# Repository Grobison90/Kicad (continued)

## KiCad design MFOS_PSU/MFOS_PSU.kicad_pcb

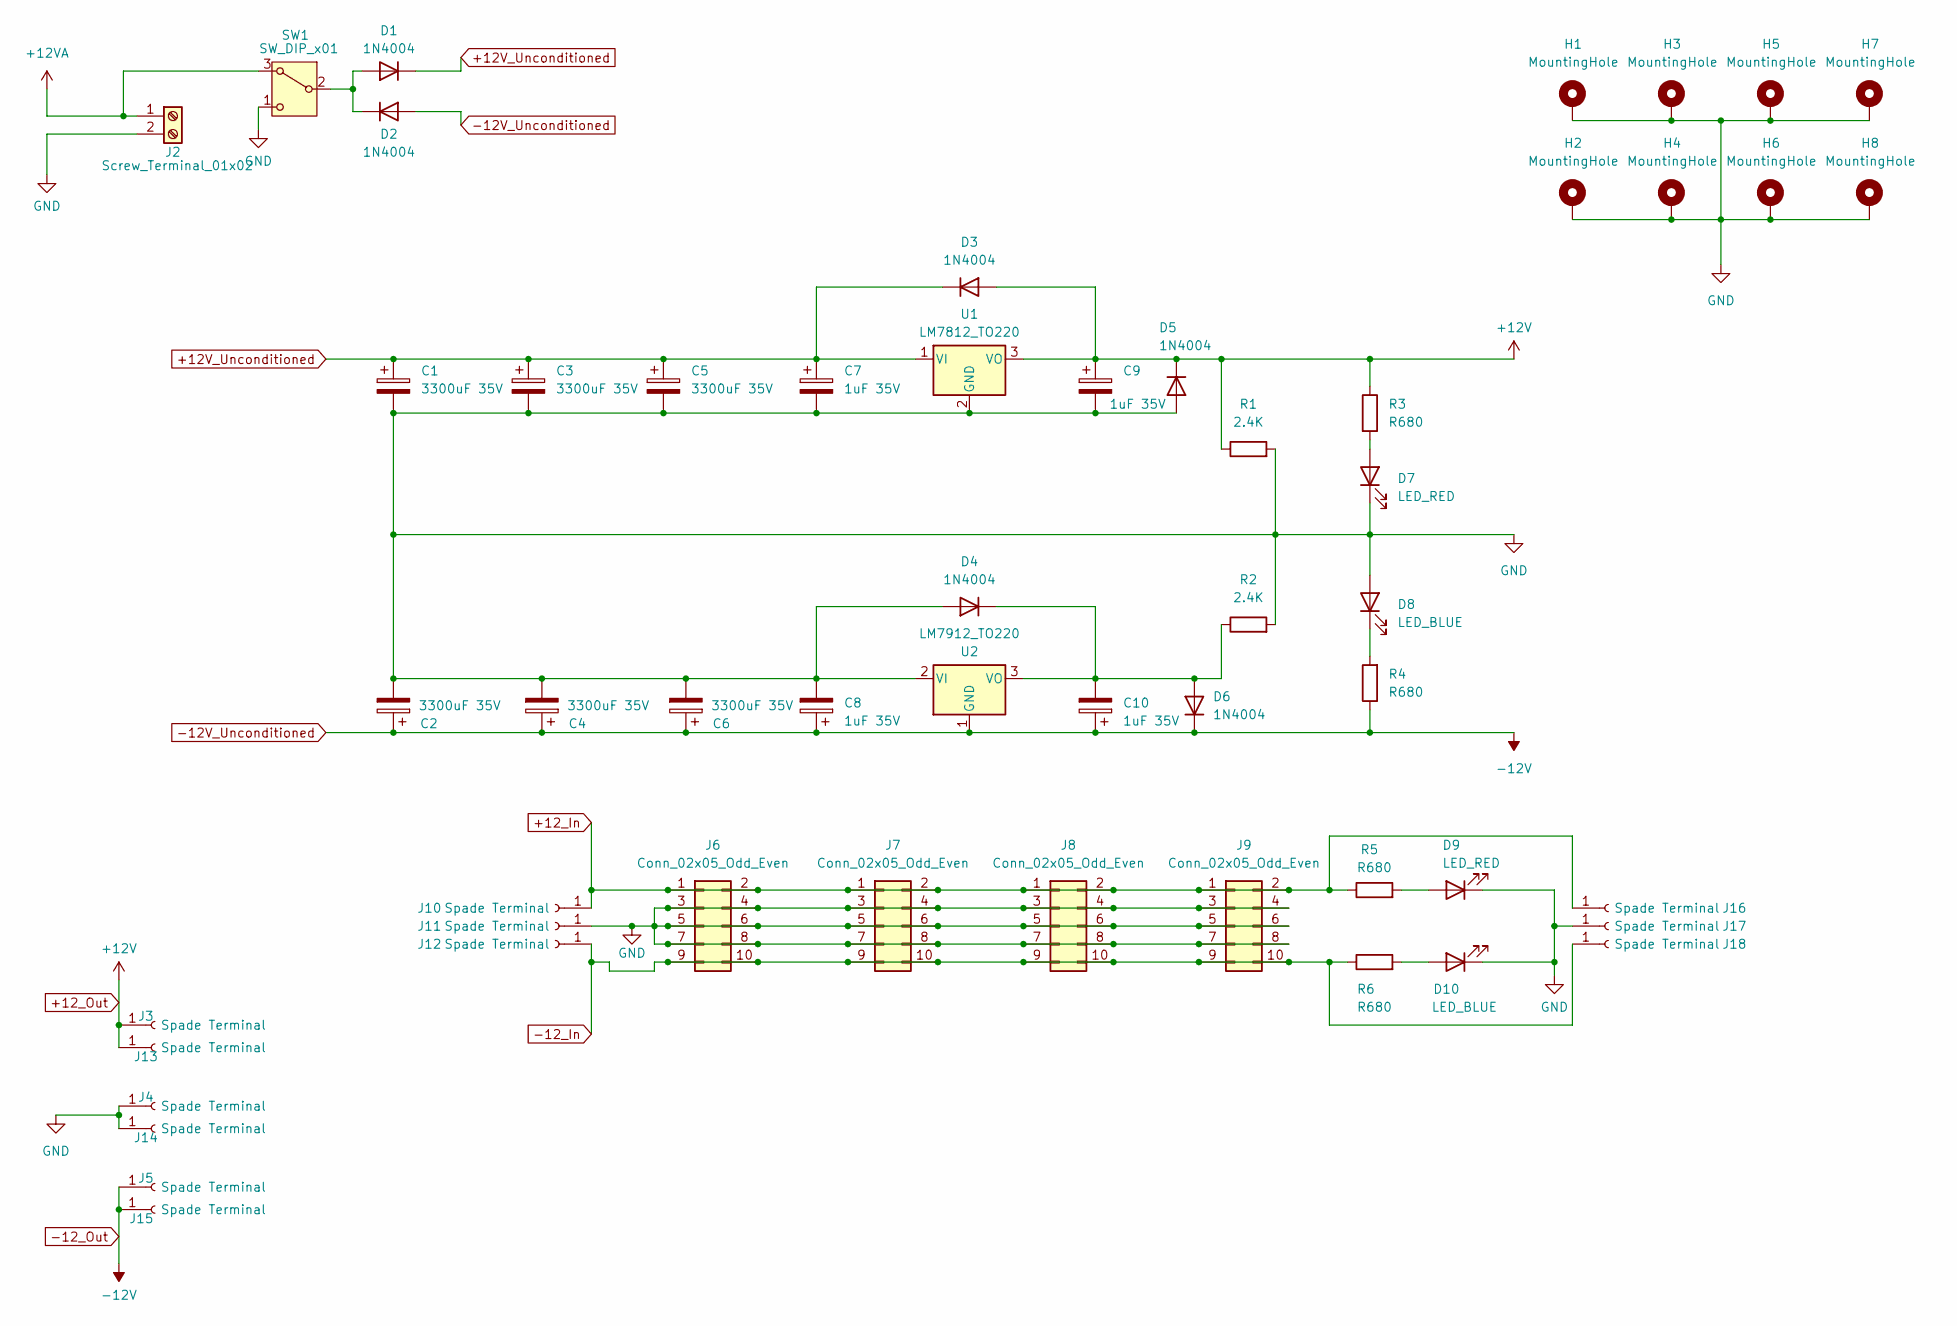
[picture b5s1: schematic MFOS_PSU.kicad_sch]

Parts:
C1, C2, C3, C4, C5, C6: 3300uF 35V; CP_Radial_D18.0mm_P7.50mm
C7, C8, C9, C10: 1uF 35V; CP_Radial_Tantal_D5.0mm_P2.50mm
D1, D2: 1N4004; D_DO-41_SOD81_P10.16mm_Horizontal
D3, D4: 1N4004; D_DO-41_SOD81_P5.08mm_Vertical_KathodeUp
D5, D6: 1N4004; D_DO-41_SOD81_P3.81mm_Vertical_KathodeUp
D7, D9: LED_RED; LED_D5.0mm
D8, D10: LED_BLUE; LED_D5.0mm
H1, H2, H3, H4, H5, H6, H7, H8: MountingHole; MountingHole_2.2mm_M2_Pad
J2: Screw_Terminal_01x02; BarrelJack_CUI_PJ-063AH_Horizontal
J3, J4, J5, J10, J11, J12, J13, J14, J15, J16, J17, J18: Spade Terminal; Spade Connector_Horizontal
J6, J7, J8, J9: Conn_02x05_Odd_Even; Eurorack Power (IDC p=2.54)_Text
R1, R2: 2.4K; R_Axial_DIN0207_L6.3mm_D2.5mm_P2.54mm_Vertical
R3, R4, R5, R6: R680; R_Axial_DIN0207_L6.3mm_D2.5mm_P2.54mm_Vertical
SW1: SW_DIP_x01; Slide Switch A-3698
U1: LM7812_TO220; TO-220-3_Vertical
U2: LM7912_TO220; TO-220-3_Vertical

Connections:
+12VA: J2.1, SW1.3 (A)
+12V_Unconditioned: C1.1, C3.1, C5.1, C7.1, D1.1 (K), D3.1 (K), U1.1 (VI)
+12_In: J6.1, J6.2, J7.1, J7.2, J8.1, J8.2, J9.1, J9.2, J10.1, J16.1, R5.1
+12_Out: C9.1, D3.2 (A), D5.1 (K), J3.1, J13.1, R1.1, R3.1, U1.3 (VO)
-12V_Unconditioned: C2.1, C4.1, C6.1, C8.1, C10.1, D2.2 (A), D6.1 (K), J5.1, J15.1, R4.1, U2.1 (GND)
-12_In: J6.9, J6.10, J7.9, J7.10, J8.9, J8.10, J9.9, J9.10, J12.1, J18.1, R6.1
GND: C1.2, C2.2, C3.2, C4.2, C5.2, C6.2, C7.2, C8.2, C9.2, D4.2 (A), D5.2 (A), D7.1 (K), D8.2 (A), D9.1 (K), D10.1 (K), H1.1, H2.1, H3.1, H4.1, H5.1, H6.1, H7.1, H8.1, J2.2, J4.1, J6.3, J6.4, J6.5, J6.6, J6.7, J6.8, J7.3, J7.4, J7.5, J7.6, J7.7, J7.8, J8.3, J8.4, J8.5, J8.6, J8.7, J8.8, J9.3, J9.4, J9.5, J9.6, J9.7, J9.8, J11.1, J14.1, J17.1, R1.2, R2.2, SW1.1 (C), U1.2 (GND), U2.2 (VI)
unnamed: D1.2 (A), D2.1 (K), SW1.2 (B)
unnamed: C10.2, D4.1 (K), D6.2 (A), R2.1, U2.3 (VO)
unnamed: D7.2 (A), R3.2
unnamed: D8.1 (K), R4.2
unnamed: D9.2 (A), R5.2
unnamed: D10.2 (A), R6.2

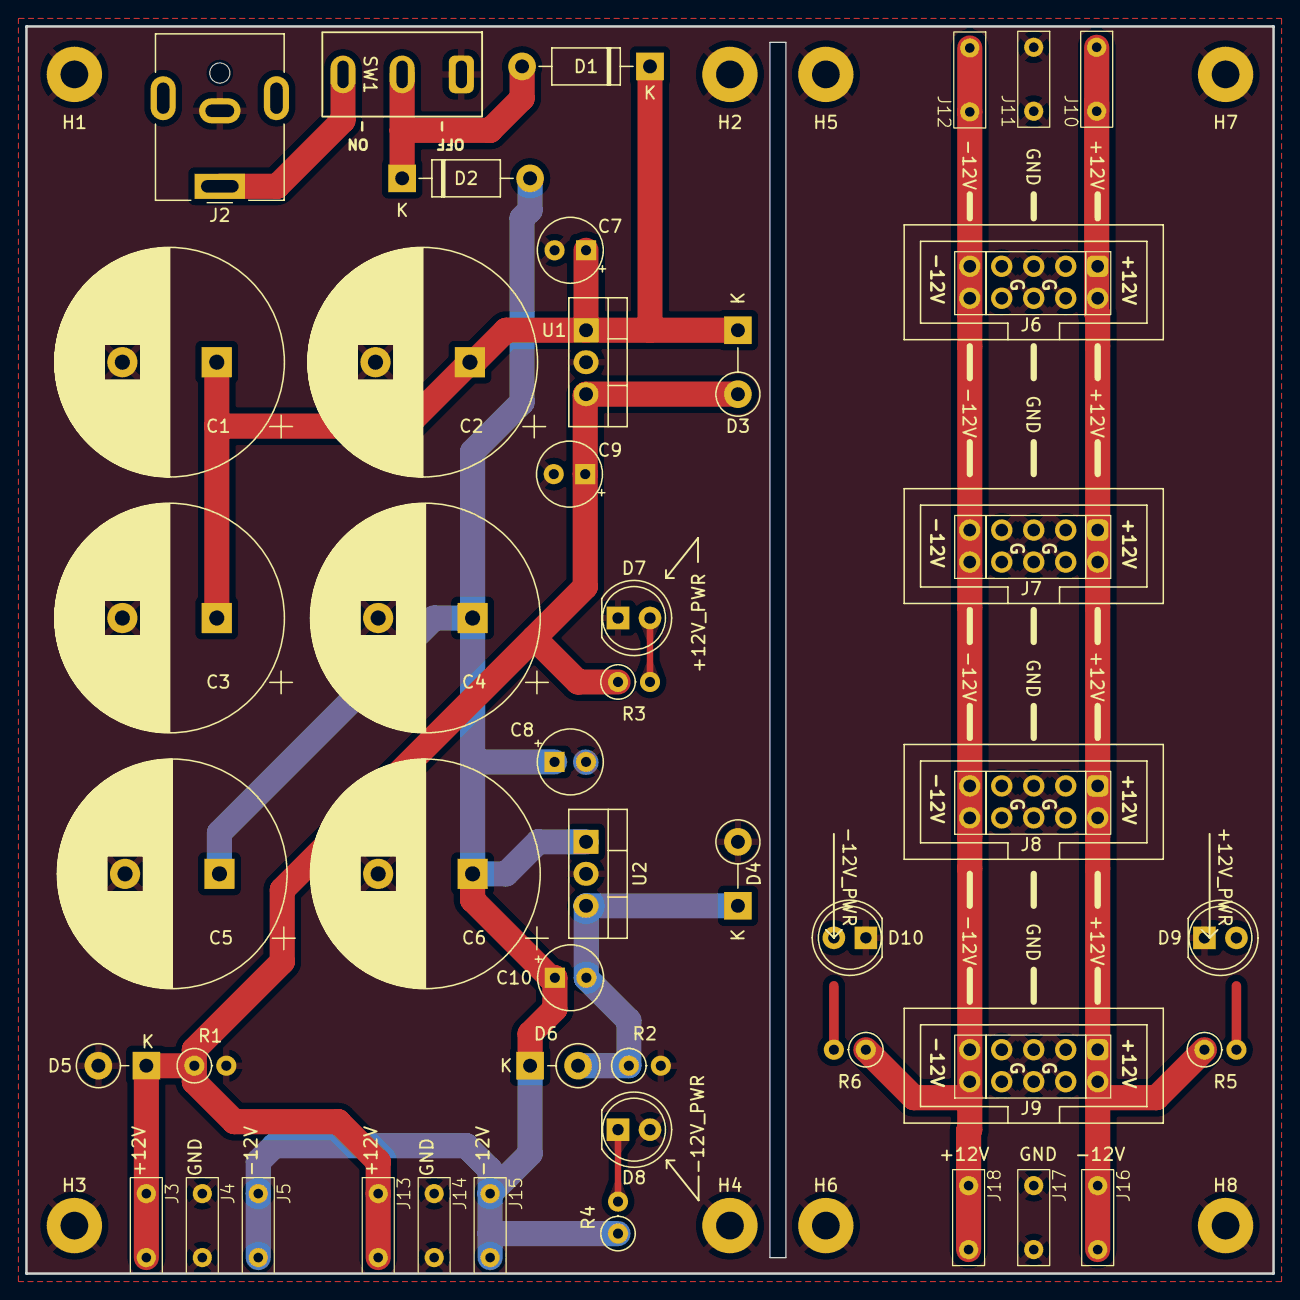
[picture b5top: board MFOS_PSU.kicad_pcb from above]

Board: 2 copper layers, 99.1 x 99.1 mm, 54 parts (0 on the bottom side), 13 nets.

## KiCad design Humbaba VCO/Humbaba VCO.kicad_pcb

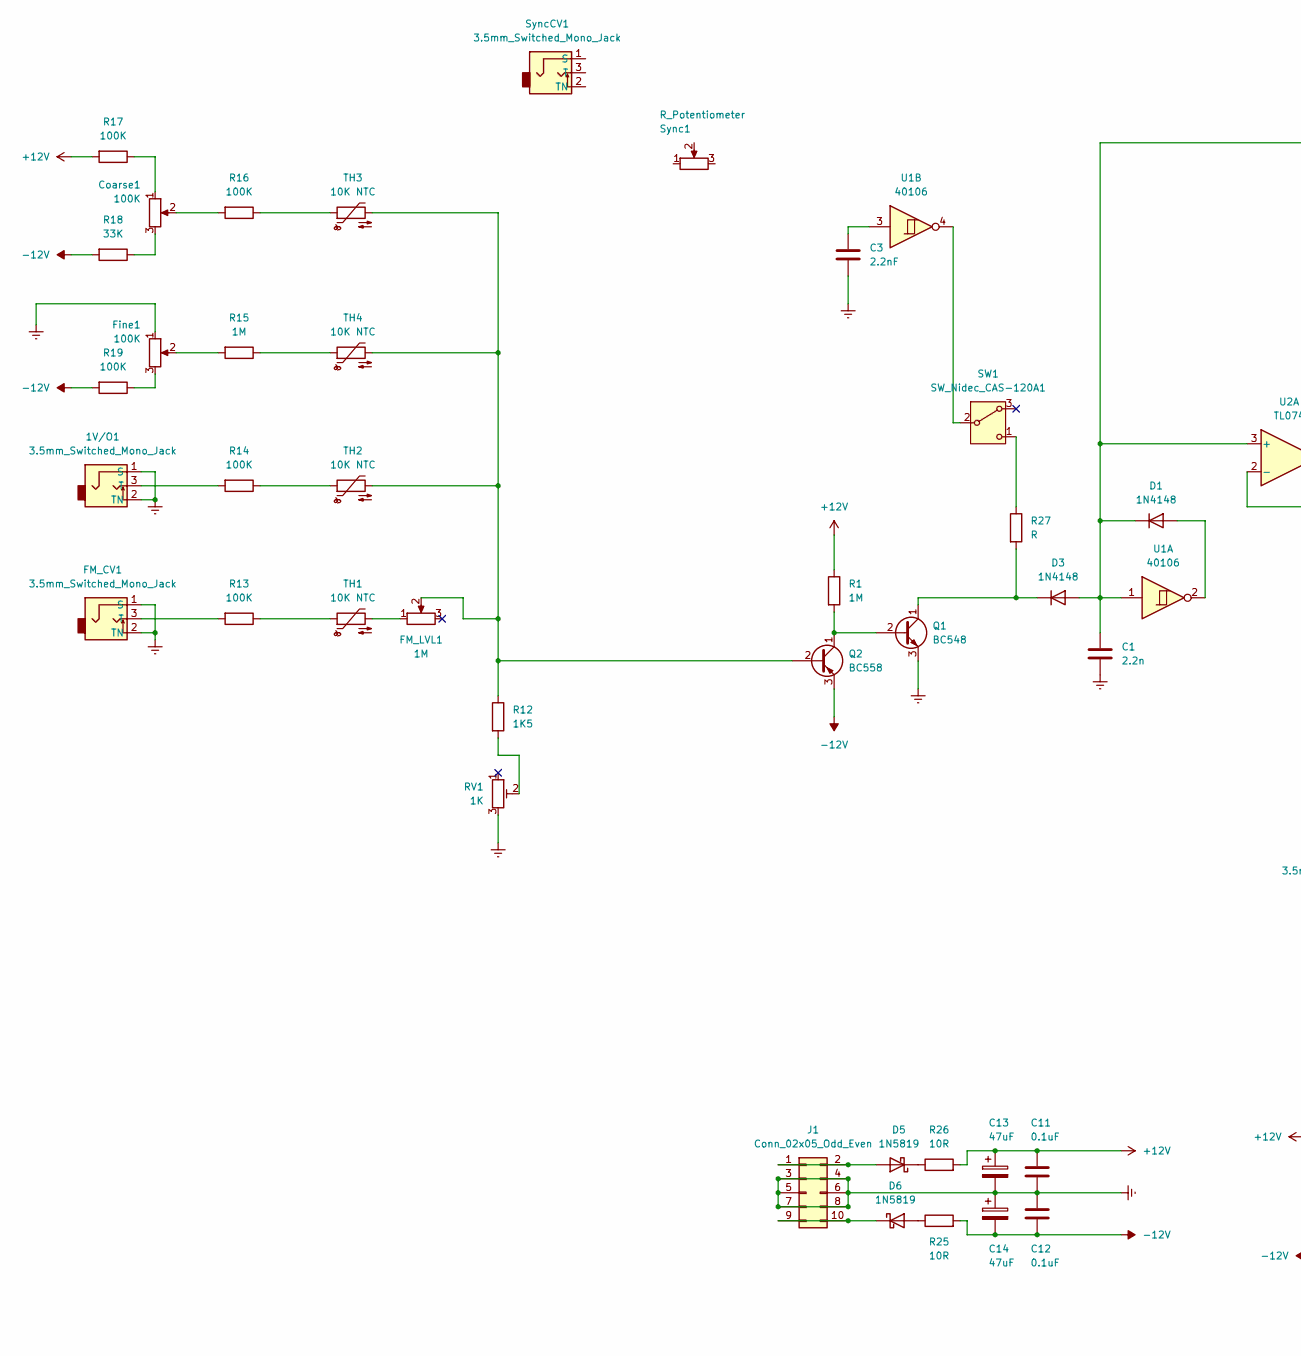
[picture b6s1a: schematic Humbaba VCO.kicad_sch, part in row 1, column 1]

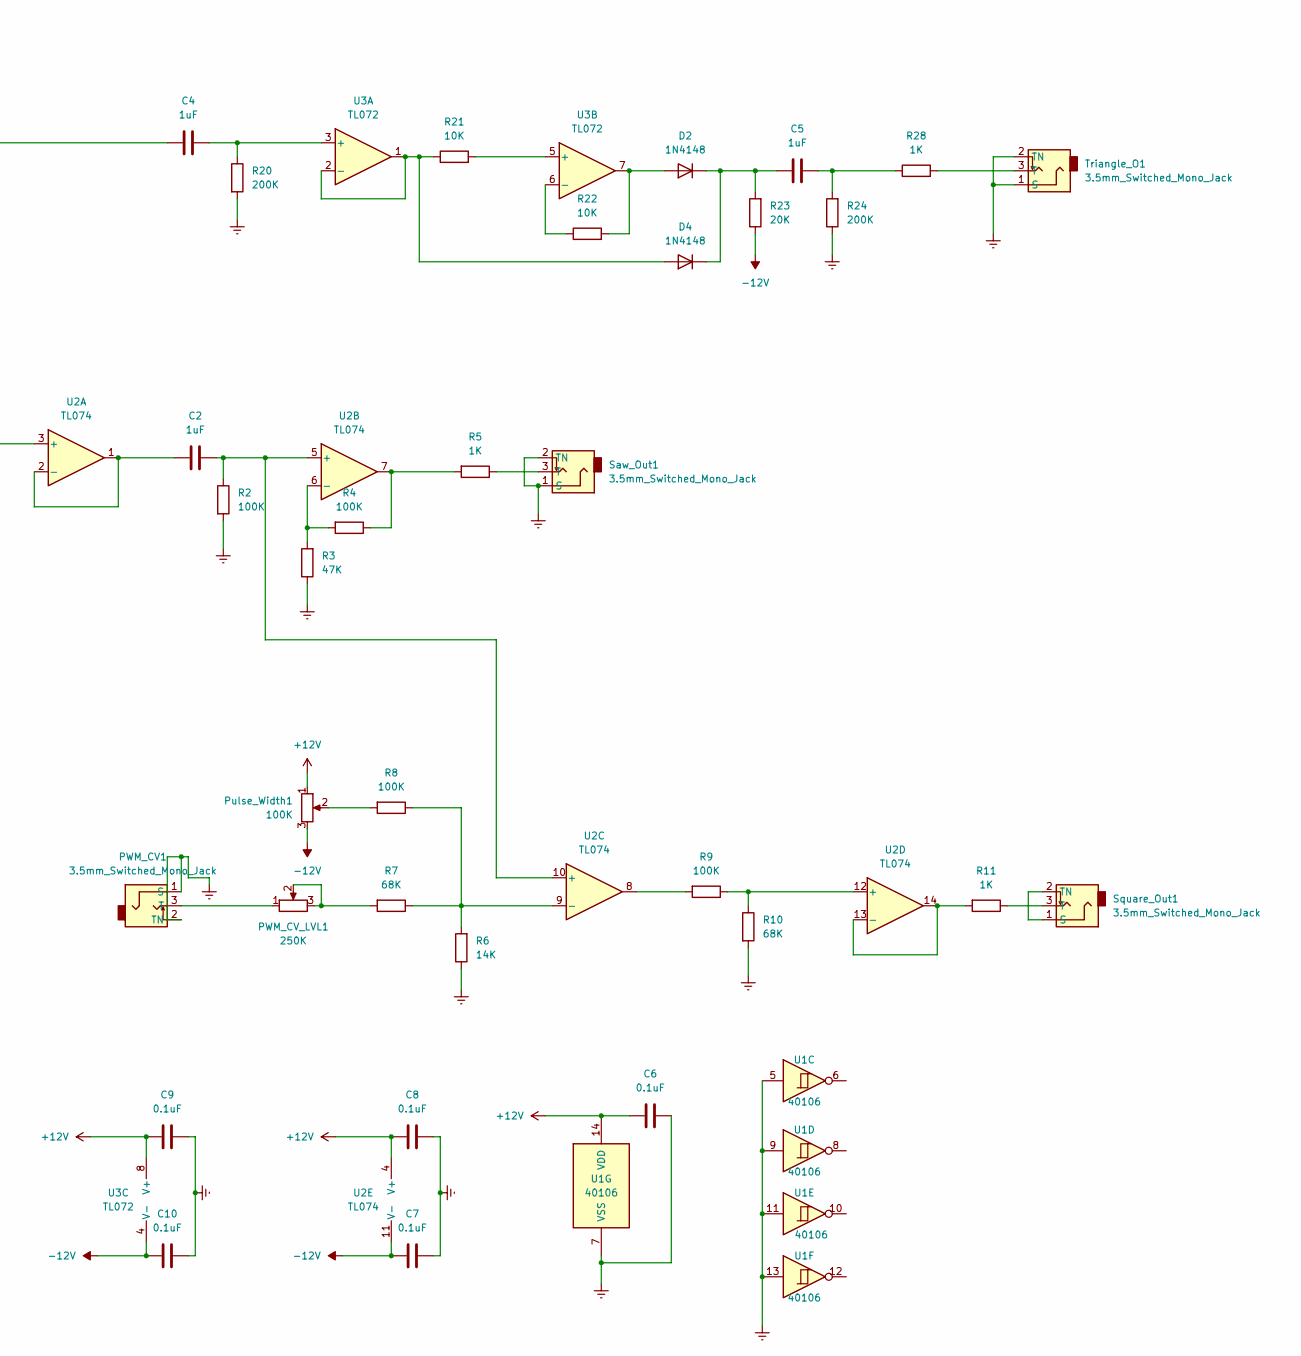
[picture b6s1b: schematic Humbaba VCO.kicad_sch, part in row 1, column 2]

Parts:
1V/O1: 3.5mm_Switched_Mono_Jack; Connector 3.5mm Mono Switched
C1: 2.2n; C_Rect_L7.0mm_W2.5mm_P5.00mm
C2, C4, C5: 1uF; C_Rect_L7.0mm_W6.0mm_P5.00mm
C3: 2.2nF; C_Rect_L7.0mm_W2.5mm_P5.00mm
C6, C7, C8, C9, C10, C11, C12: 0.1uF; C_0805_2012Metric
C13, C14: 47uF; CP_Elec_6.3x5.8
Coarse1: 100K; Potentiometer_Alpha_RD901F-40-00D_Single_Vertical
D1, D2, D3, D4: 1N4148; D_SOD-323_HandSoldering
D5, D6: 1N5819; D_DO-41_SOD81_P10.16mm_Horizontal
FM_CV1: 3.5mm_Switched_Mono_Jack; Connector 3.5mm Mono Switched
FM_LVL1: 1M; Potentiometer_Alpha_RD901F-40-00D_Single_Vertical
Fine1: 100K; Potentiometer_Alpha_RD901F-40-00D_Single_Vertical
J1: Conn_02x05_Odd_Even; IDC-Header_2x05_P2.54mm_Vertical
PWM_CV1: 3.5mm_Switched_Mono_Jack; Connector 3.5mm Mono Switched
PWM_CV_LVL1: 250K; Potentiometer_Alpha_RD901F-40-00D_Single_Vertical
Pulse_Width1: 100K; Potentiometer_Alpha_RD901F-40-00D_Single_Vertical
Q1: BC548; TO-92_Inline
Q2: BC558; TO-92_Inline
R1, R15: 1M; R_0805_2012Metric
R2, R4, R8, R9, R13, R14, R16, R17, R19: 100K; R_0805_2012Metric
R3: 47K; R_0805_2012Metric
R5, R11, R28: 1K; R_0805_2012Metric
R6: 14K; R_0805_2012Metric
R7, R10: 68K; R_0805_2012Metric
R12: 1K5; R_0805_2012Metric
R18: 33K; R_0805_2012Metric
R20, R24: 200K; R_0805_2012Metric
R21, R22: 10K; R_0805_2012Metric
R23: 20K; R_0805_2012Metric
R25, R26: 10R; R_0805_2012Metric
R27: R; R_0805_2012Metric
RV1: 1K; Potentiometer_Bourns_3386C_Horizontal
SW1: SW_Nidec_CAS-120A1; SPDT ON-ON sw
Saw_Out1: 3.5mm_Switched_Mono_Jack; Connector 3.5mm Mono Switched
Square_Out1: 3.5mm_Switched_Mono_Jack; Connector 3.5mm Mono Switched
Sync1: R_Potentiometer; Potentiometer_Alpha_RD901F-40-00D_Single_Vertical
SyncCV1: 3.5mm_Switched_Mono_Jack; Connector 3.5mm Mono Switched
TH1, TH2, TH3, TH4: 10K NTC; Thermistor
Triangle_O1: 3.5mm_Switched_Mono_Jack; Connector 3.5mm Mono Switched
U1: 40106; DIP-14_W7.62mm_Socket
U2: TL074; HTSSOP-14-1EP_4.4x5mm_P0.65mm_EP3.4x5mm_Mask3x3.1mm
U3: TL072; SO-8_3.9x4.9mm_P1.27mm

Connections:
+12V: C6.1, C8.1, C9.1, C11.1, C13.1, Pulse_Width1.1, R1.1, R17.2, R26.2, U1.14 (VDD), U2.4 (V+), U3.8 (V+)
-12V: C7.2, C10.1, C12.2, C14.2, Pulse_Width1.3, Q2.3 (E), R18.2, R19.2, R23.1, R25.2, U2.11 (V-), U3.4 (V-)
Earth: 1V/O1.1 (S), 1V/O1.2 (TN), C1.2, C3.2, C6.2, C7.1, C8.2, C9.2, C10.2, C11.2, C12.1, C13.2, C14.1, FM_CV1.1 (S), FM_CV1.2 (TN), Fine1.1, J1.3, J1.4, J1.5, J1.6, J1.7, J1.8, PWM_CV1.1 (S), PWM_CV1.2 (TN), Q1.3 (E), R2.2, R3.1, R6.1, R10.2, R20.2, R24.1, RV1.3, Saw_Out1.1 (S), Saw_Out1.2 (TN), Triangle_O1.1 (S), Triangle_O1.2 (TN), U1.5, U1.7 (VSS), U1.9, U1.11, U1.13
unnamed: 1V/O1.3 (T), R14.2
unnamed: C3.1, U1.3
unnamed: C5.2, R24.2, R28.1
unnamed: Coarse1.1, R17.1
unnamed: Coarse1.2, R16.2
unnamed: Coarse1.3, R18.1
unnamed: D1.2 (A), U1.2
unnamed: C1.1, C4.1, D1.1 (K), D3.2 (A), U1.1, U2.3 (+)
unnamed: D2.2 (A), R22.2, U3.7
unnamed: C5.1, D2.1 (K), D4.1 (K), R23.2
unnamed: D3.1 (K), Q1.1 (C), R27.2
unnamed: D4.2 (A), R21.1, U3.1, U3.2 (-)
unnamed: D5.2 (A), J1.1, J1.2
unnamed: D5.1 (K), R26.1
unnamed: D6.2 (A), R25.1
unnamed: D6.1 (K), J1.9, J1.10
unnamed: FM_CV1.3 (T), R13.2
unnamed: FM_LVL1.1, TH1.2
unnamed: Fine1.2, R15.2
unnamed: Fine1.3, R19.1
unnamed: PWM_CV1.3 (T), PWM_CV_LVL1.1
unnamed: PWM_CV_LVL1.2, PWM_CV_LVL1.3, R7.2
unnamed: Pulse_Width1.2, R8.2
unnamed: Q1.2 (B), Q2.1 (C), R1.2
unnamed: R4.1, R5.2, U2.7
unnamed: R9.2, U2.8
unnamed: R13.1, TH1.1
unnamed: R14.1, TH2.1
unnamed: R15.1, TH4.1
unnamed: R16.1, TH3.1
unnamed: SW1.2 (B), U1.4
unnamed: R27.1, SW1.1 (C)
unnamed: R5.1, Saw_Out1.3 (T)
unnamed: Square_Out1.1 (S), Square_Out1.2 (TN)
unnamed: R11.1, Square_Out1.3 (T)
unnamed: R28.2, Triangle_O1.3 (T)
unnamed: C2.1, U2.1, U2.2 (-)
unnamed: C2.2, R2.1, U2.5 (+), U2.10 (+)
unnamed: R3.2, R4.2, U2.6 (-)
unnamed: R6.2, R7.1, R8.1, U2.9 (-)
unnamed: R9.1, R10.1, U2.12 (+)
unnamed: R11.2, U2.13 (-), U2.14
unnamed: C4.2, R20.1, U3.3 (+)
unnamed: R21.2, U3.5 (+)
unnamed: R22.1, U3.6 (-)

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
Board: 2 copper layers, 73 parts (57 on the bottom side), 50 nets, no tracks yet.

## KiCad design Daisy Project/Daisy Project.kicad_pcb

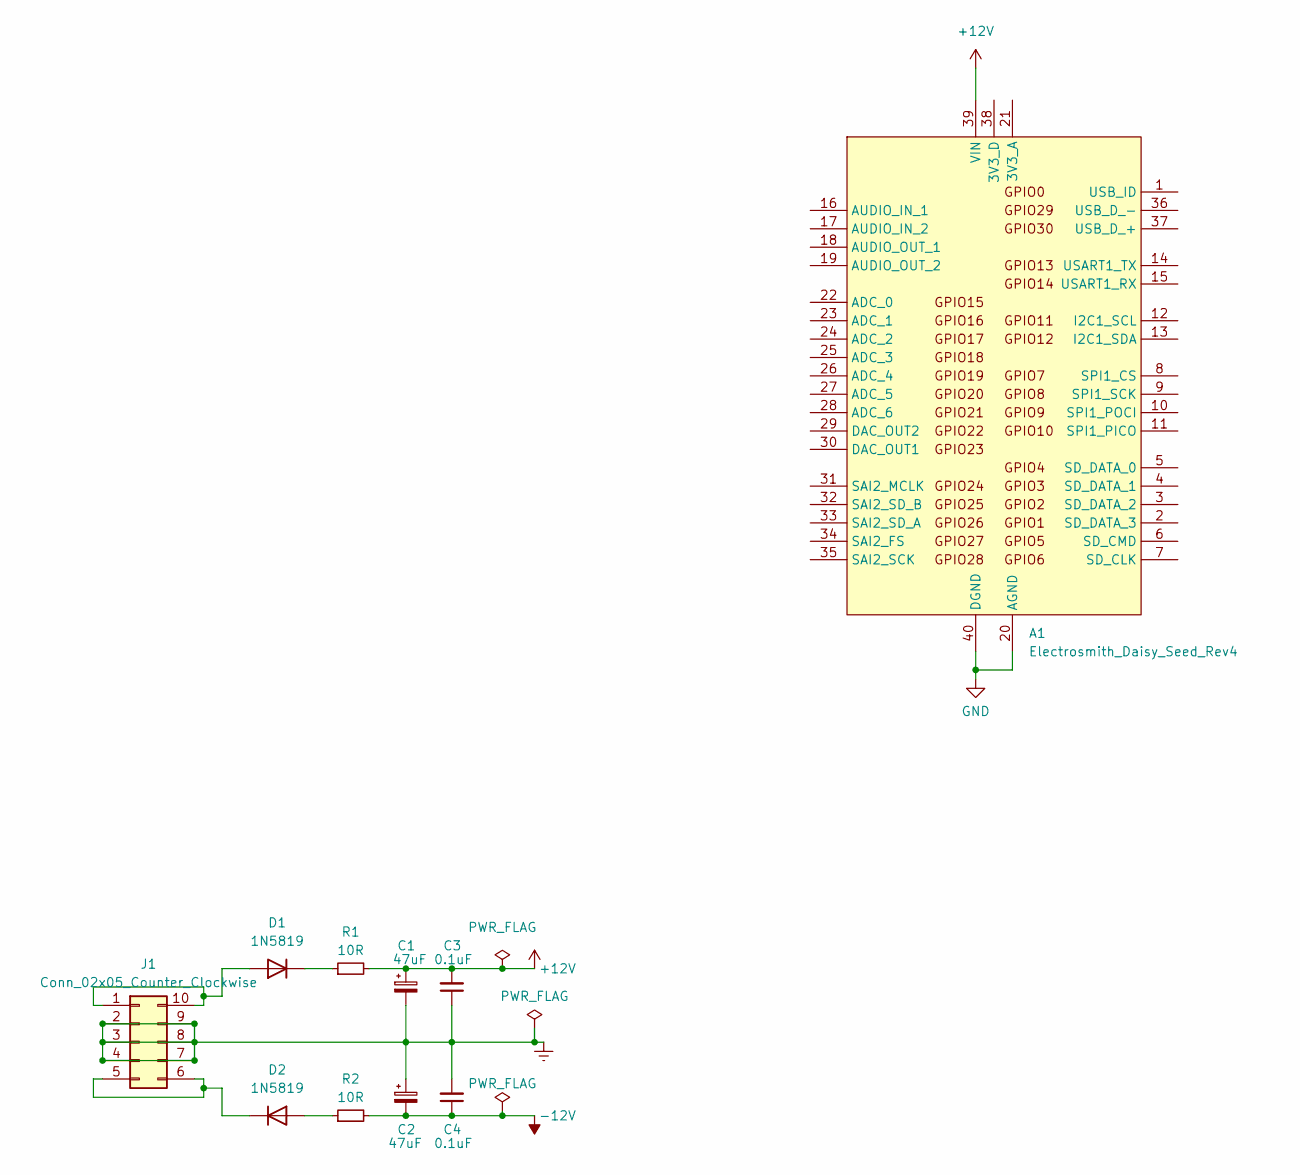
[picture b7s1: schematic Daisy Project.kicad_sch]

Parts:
A1: Electrosmith_Daisy_Seed_Rev4; Electrosmith_Daisy_Seed
C1, C2: 47uF; CP_Radial_D5.0mm_P2.50mm
C3, C4: 0.1uF; C_Disc_D6.0mm_W2.5mm_P5.00mm
D1, D2: 1N5819; D_DO-35_SOD27_P7.62mm_Horizontal
J1: Conn_02x05_Counter_Clockwise; PinHeader_2x05_P1.27mm_Vertical_MyVersion
R1, R2: 10R; R_Axial_DIN0207_L6.3mm_D2.5mm_P2.54mm_Vertical

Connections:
+12V: A1.39 (VIN), C1.1, C3.2, R1.2
-12V: C2.2, C4.1, R2.2
Earth: C1.2, C2.1, C3.1, C4.2, J1.2, J1.3, J1.4, J1.7, J1.8, J1.9
GND: A1.20 (AGND), A1.40 (DGND)
unnamed: D1.2 (A), J1.1, J1.10
unnamed: D1.1 (K), R1.1
unnamed: D2.2 (A), R2.1
unnamed: D2.1 (K), J1.5, J1.6

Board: 2 copper layers, 10 parts (1 on the bottom side), 8 nets, no tracks yet.

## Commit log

2025-03-31 Initial Commit 3/21/25
2025-03-31 PCB design from scratch now.
2025-03-31 PCB from scratch now.
2025-04-20 Working on Seq Rev 3.
2025-04-26 4/26/25
2025-07-15 7-15-2025
